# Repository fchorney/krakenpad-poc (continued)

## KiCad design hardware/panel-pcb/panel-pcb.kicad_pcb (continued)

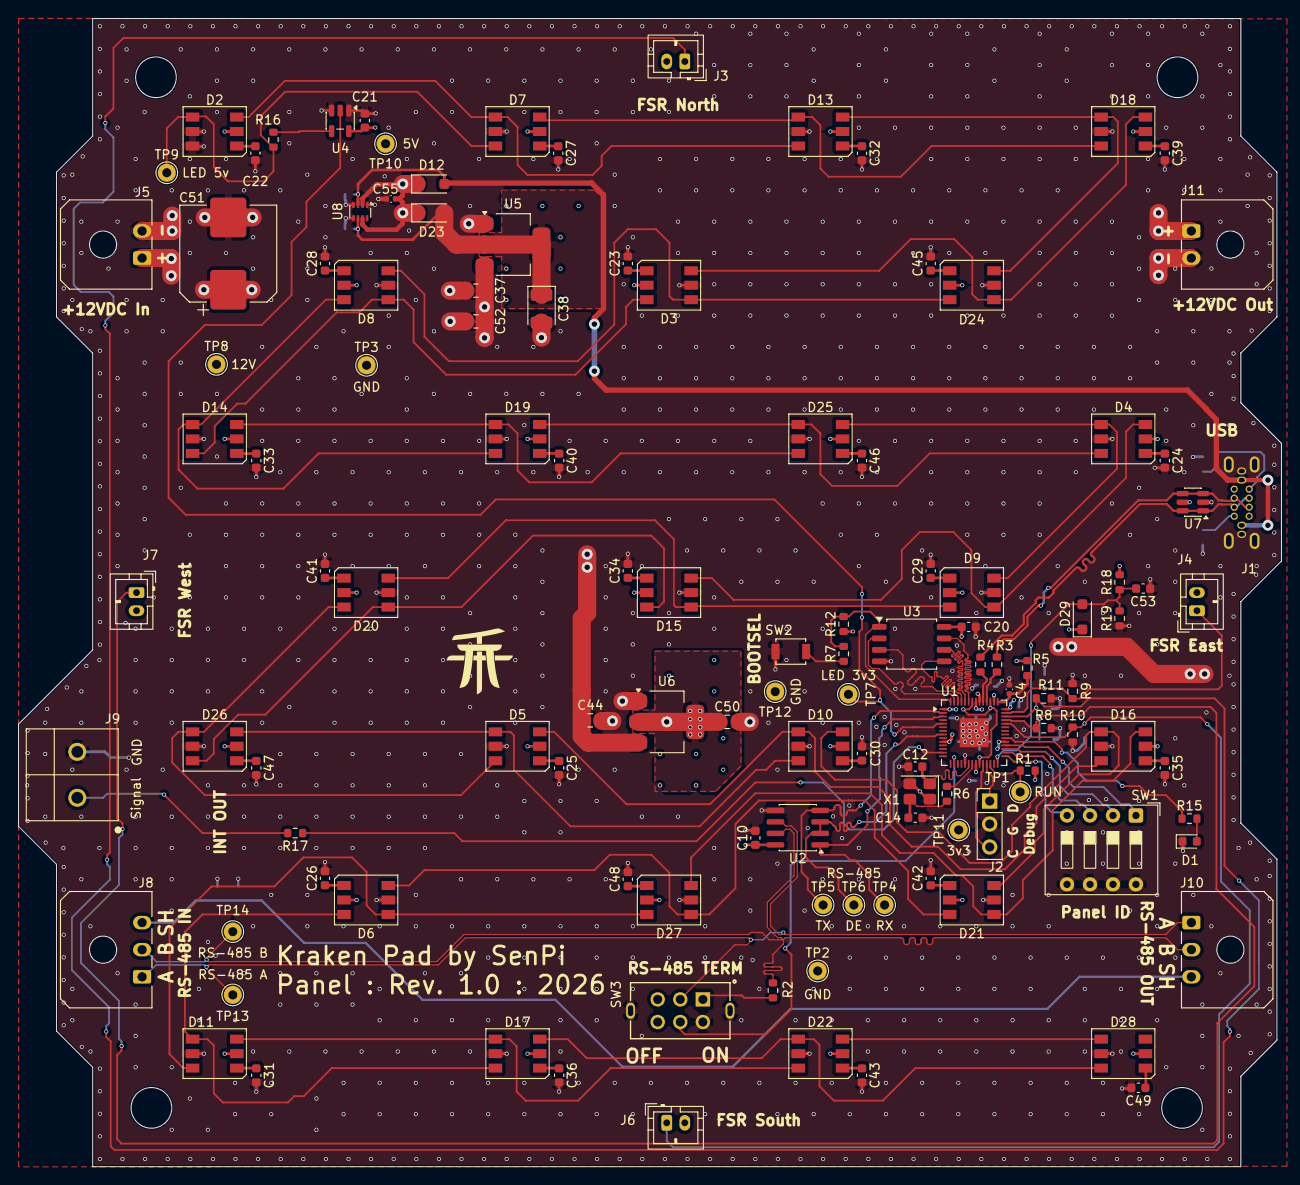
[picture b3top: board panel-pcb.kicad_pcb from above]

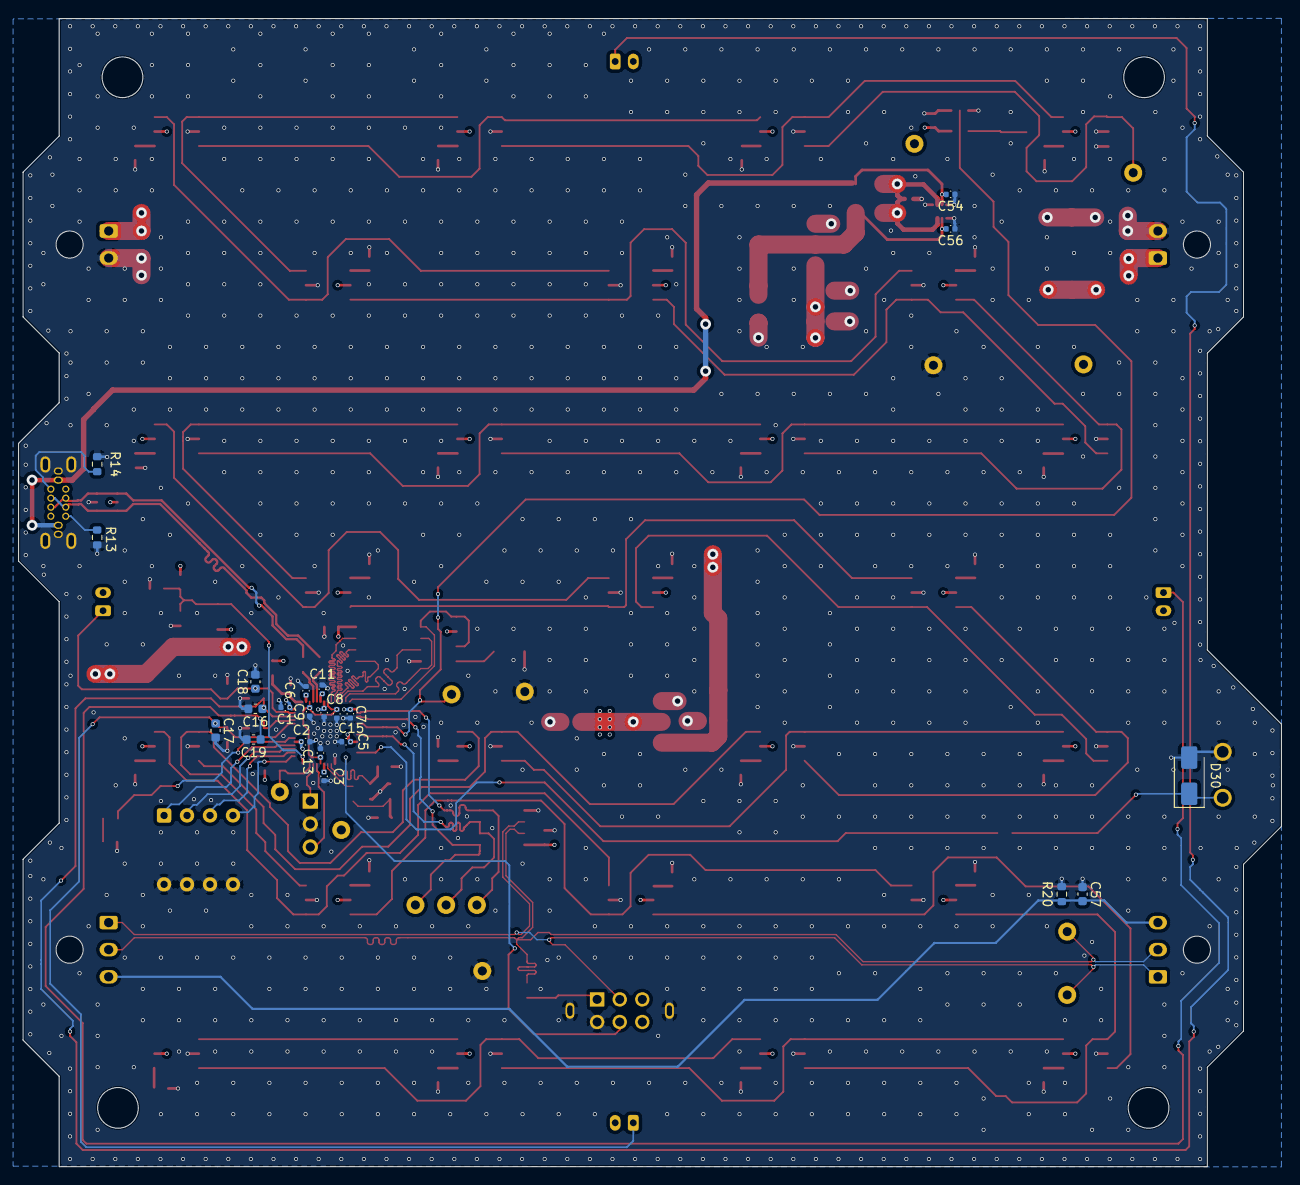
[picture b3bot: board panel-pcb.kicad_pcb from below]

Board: 4 copper layers, 139.7 x 127.0 mm, 144 parts (22 on the bottom side), 100 nets.

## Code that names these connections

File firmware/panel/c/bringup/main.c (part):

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#include "ws2812.pio.h"

// ── As-built pin map (docs/DUAL_PANEL.md → "RP2040 (U306) GPIO map") ─────────
#define PIN_RS485_TX    0
#define PIN_RS485_RX    1
#define PIN_RS485_DE    4    // DE + ~RE tied; HIGH = transmit. Also TP306.
#define PIN_TERM_SENSE  10   // LOW = terminated (SW202 pole B, closes to GND)
#define PIN_LED_DATA    11   // → U301 shifter → R301 330R → carrier
#define PIN_DEBUG_LED   16   // carrier D202/R204
#define PIN_SENSE_12V   17   // R313 100k / R314 33k divider. DIGITAL, not ADC.
#define PIN_DIP_ID3     18   // NOTE the reversal: GPIO18 is bit 3, GPIO21 bit 0
#define PIN_DIP_ID2     19
#define PIN_DIP_ID1     20
#define PIN_DIP_ID0     21
#define PIN_INT_OUT     22   // emulated open-drain, sole gameplay press path

#define NUM_FSR   4
#define NUM_LEDS  25

// GPIO26..29 = ADC0..3. Names are the physical panel edge each lands on; the
// carrier connector for each is listed so a swapped pair is identifiable.
static const uint  FSR_GPIO[NUM_FSR] = {26, 27, 28, 29};
static const char *FSR_NAME[NUM_FSR] = {"South", "West", "North", "East"};
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static volatile bool     g_12v_edge_flag = false;   // set by timer, printed by main
static volatile uint32_t g_12v_edge_ms   = 0;

static bool sense_12v_raw(void) { return gpio_get(PIN_SENSE_12V); }

static bool sense_timer_cb(repeating_timer_t *t) {
    (void)t;
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static void sense_pull_probe(void) {
    printf("  SENSE_12V under each pad pull configuration:\n");

    gpio_disable_pulls(PIN_SENSE_12V);            sleep_ms(5);
    bool none = gpio_get(PIN_SENSE_12V);
    gpio_pull_down(PIN_SENSE_12V);                sleep_ms(5);
    bool down = gpio_get(PIN_SENSE_12V);
    gpio_pull_up(PIN_SENSE_12V);                  sleep_ms(5);
    bool up   = gpio_get(PIN_SENSE_12V);
    gpio_disable_pulls(PIN_SENSE_12V);            sleep_ms(5);

    printf("    pulls off   : %d   <- the configuration firmware must use\n", none);
    printf("    pull-down   : %d\n", down);
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// So "released" was hi-Z *plus a ~45k pull-down*, which fights the master's 10k
// pull-up: measured 2.7V instead of 3.3V on board DE6558A69754442F. Still above
// the Teensy's VIH, so it would have worked — with 0.4V of noise margin on the
// sole gameplay input path instead of 1.0V. This is the GPIO17 trap on a second
// pin, and it is invisible without an external pull-up on the bench.
static void int_out_init(void) {
    gpio_init(PIN_INT_OUT);
    gpio_disable_pulls(PIN_INT_OUT);       // released must be TRUE hi-Z
    gpio_put(PIN_INT_OUT, 0);              // latch low, ready for the dir flip
    gpio_set_dir(PIN_INT_OUT, GPIO_IN);    // released = hi-Z
}
static void int_out_assert(void)  { gpio_set_dir(PIN_INT_OUT, GPIO_OUT); }
static void int_out_release(void) { gpio_set_dir(PIN_INT_OUT, GPIO_IN);  }

// ── DIP + termination ───────────────────────────────────────────────────────
// No board resistors on either net — internal pull-ups are load-bearing.
// Switch closes to GND, so a CLOSED (ON) position reads 0. Panel ID 0 therefore
// means all four switches ON, and an untouched all-OFF switch reads 15.
static uint8_t dip_read(void) {
    return (uint8_t)((gpio_get(PIN_DIP_ID3) << 3) |
                     (gpio_get(PIN_DIP_ID2) << 2) |
                     (gpio_get(PIN_DIP_ID1) << 1) |
                      gpio_get(PIN_DIP_ID0));
}

static const char *dip_meaning(uint8_t v) {
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
// ── LED test — gated on SENSE_12V ───────────────────────────────────────────
// U301 runs from +5VDC, which is live from VBUS alone, so on USB-only power it
// will happily drive LED_DATA_5V into WS2815 DIN pins whose 12V rail is dead,
// forward-biasing their input protection. R301 (330R) keeps that non-destructive
// but it is not a valid test either. This gate is what GPIO17 is FOR.
static PIO  led_pio = pio0;
static uint led_sm;
static bool led_ready = false;
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static void led_init(void) {
    uint offset = pio_add_program(led_pio, &ws2812_program);
    led_sm = pio_claim_unused_sm(led_pio, true);
    ws2812_program_init(led_pio, led_sm, offset, PIN_LED_DATA, 800000.0f, false);
    led_ready = true;
}

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// ── Status ──────────────────────────────────────────────────────────────────
static void print_status(void) {
    uint8_t dip = dip_read();
    bool term    = !gpio_get(PIN_TERM_SENSE);   // LOW = terminated
    bool mated   = (dip != 15) || term;         // best-effort hint, not proof

    printf("\n--- status @ %lu ms ---\n", (unsigned long)to_ms_since_boot(get_absolute_time()));
    printf("  SENSE_12V     : %s  (raw pin %d, %lu edge(s) since boot)\n",
           g_12v_present ? "12V PRESENT" : "12V ABSENT",
           sense_12v_raw(), (unsigned long)g_12v_edges);
    printf("  DIP           : %u  (0b%d%d%d%d, %s)\n", dip,
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}

static void dip_watch(void) {
    printf("  toggle one position at a time. GPIO18 is bit 3 and GPIO21 is bit 0 —\n"
           "  the order is REVERSED relative to SW201's 1-4 labelling, and a closed\n"
           "  switch reads 0. This is the one place to prove that physically.\n"
           "  Any key stops.\n");
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           "  Do NOT try to read this phase on a handheld meter; it will show you\n"
           "  the ~2.6V duty-cycle average and look like a fault.\n");
    for (int i = 0; i < 5; i++) {
        int_out_assert();  gpio_put(PIN_DEBUG_LED, 1); sleep_ms(200);
        int_out_release(); gpio_put(PIN_DEBUG_LED, 0); sleep_ms(800);
    }

    printf("\n  Phase 2: steady dwells, %d s each — THIS is the one to meter.\n"
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           "  both readings are ~0V and distinguish nothing.\n", INT_DWELL_MS / 1000);

    printf("\n  >>> ASSERTED (driven LOW) — read the meter now. Expect ~0V.\n");
    int_out_assert(); gpio_put(PIN_DEBUG_LED, 1);
    sleep_ms(INT_DWELL_MS);

    printf("  >>> RELEASED (hi-Z) — read again. Expect ~3.3V via the pull-up.\n"
           "      If this reads ~0V the pin is stuck driven low. If it reads 3.3V\n"
           "      with the pull-up REMOVED, firmware is driving it high — the bug\n"
           "      this test exists to catch.\n");
    int_out_release(); gpio_put(PIN_DEBUG_LED, 0);
    sleep_ms(INT_DWELL_MS);

    printf("\n  done, released (hi-Z).\n");
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    crc = crc8_update(crc, len);
    for (uint8_t i = 0; i < len; i++) crc = crc8_update(crc, pay[i]);

    gpio_put(PIN_RS485_DE, 1);
    busy_wait_us(2);                      // driver enabled before the start bit
    uart_write_blocking(uart0, hdr, 4);
    if (len) uart_write_blocking(uart0, pay, len);
    uart_write_blocking(uart0, &crc, 1);
    uart_tx_wait_blocking(uart0);         // BUSY flag, not FIFO-empty — see (3)
    busy_wait_us(12);                     // ~1 char at 1 Mbps of slack
    gpio_put(PIN_RS485_DE, 0);            // back to receive
    rs_last_tx_us = time_us_32();
}

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// the watchdog reset, and the bootloader clears it once read.
static void reboot_into_bootloader(void) {
    int_out_release();
    gpio_put(PIN_RS485_DE, 0);
    watchdog_hw->scratch[0] = FW_HOLD_MAGIC;
    watchdog_reboot(0, 0, 10);
    while (true) tight_loop_contents();
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        put_u32(&r[4], to_ms_since_boot(get_absolute_time()) / 1000u);
        r[8] = g_reset_flags;
        r[9] = (uint8_t)((g_12v_present            ? 1u << 0 : 0) |
                         (!gpio_get(PIN_TERM_SENSE) ? 1u << 1 : 0) |
                         (g_auto_int               ? 1u << 2 : 0) |
                         (g_led_echo               ? 1u << 3 : 0) |
                         (g_int_asserted           ? 1u << 4 : 0));
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
static void rs485_init(void) {
    uart_init(uart0, RS485_BAUD);
    gpio_set_function(PIN_RS485_TX, GPIO_FUNC_UART);
    gpio_set_function(PIN_RS485_RX, GPIO_FUNC_UART);
    // ⚠ Idle-bias the RX pin. While WE transmit, DE (tied to ~RE) disables the
    // THVD1450's receiver and RO goes high-impedance, so this pin floats. When
    // DE drops and RO drives again, the transition is seen as a false start bit
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    // reply, but it is noise in a counter that should mean something. An
    // internal pull-up holds the line at idle-mark through the Hi-Z window and
    // removes the glitch at its source, with no board change.
    gpio_pull_up(PIN_RS485_RX);
    uart_set_format(uart0, 8, 1, UART_PARITY_NONE);
    uart_set_fifo_enabled(uart0, true);
    uart_set_hw_flow(uart0, false, false);
    gpio_put(PIN_RS485_DE, 0);
    irq_set_exclusive_handler(UART0_IRQ, rs485_rx_irq);
    irq_set_enabled(UART0_IRQ, true);
    // NOTE: RX interrupts are enabled/disabled by the 'R' toggle, not here. With
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    stdio_init_all();

    // SENSE_12V: pulls OFF, deliberately and first. See sense_pull_probe().
    gpio_init(PIN_SENSE_12V);
    gpio_set_dir(PIN_SENSE_12V, GPIO_IN);
    gpio_disable_pulls(PIN_SENSE_12V);

    // No external pull-ups exist on these nets. Unmated they read all-ones.
    const uint pu[] = {PIN_TERM_SENSE, PIN_DIP_ID0, PIN_DIP_ID1, PIN_DIP_ID2, PIN_DIP_ID3};
    for (uint i = 0; i < count_of(pu); i++) {
        gpio_init(pu[i]); gpio_set_dir(pu[i], GPIO_IN); gpio_pull_up(pu[i]);
    }

    gpio_init(PIN_DEBUG_LED); gpio_set_dir(PIN_DEBUG_LED, GPIO_OUT);
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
